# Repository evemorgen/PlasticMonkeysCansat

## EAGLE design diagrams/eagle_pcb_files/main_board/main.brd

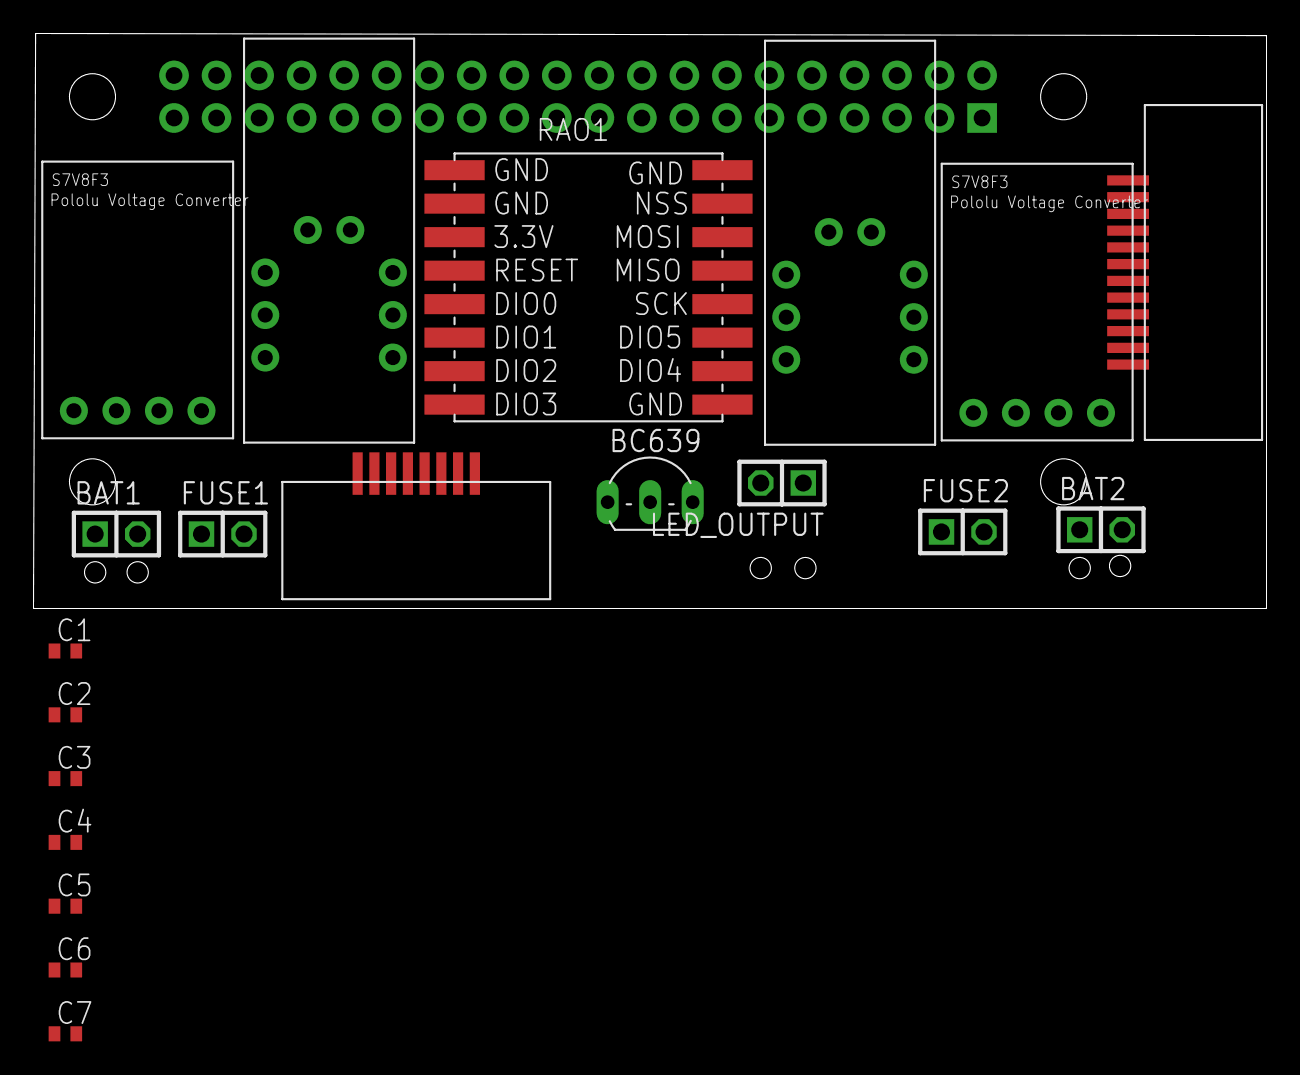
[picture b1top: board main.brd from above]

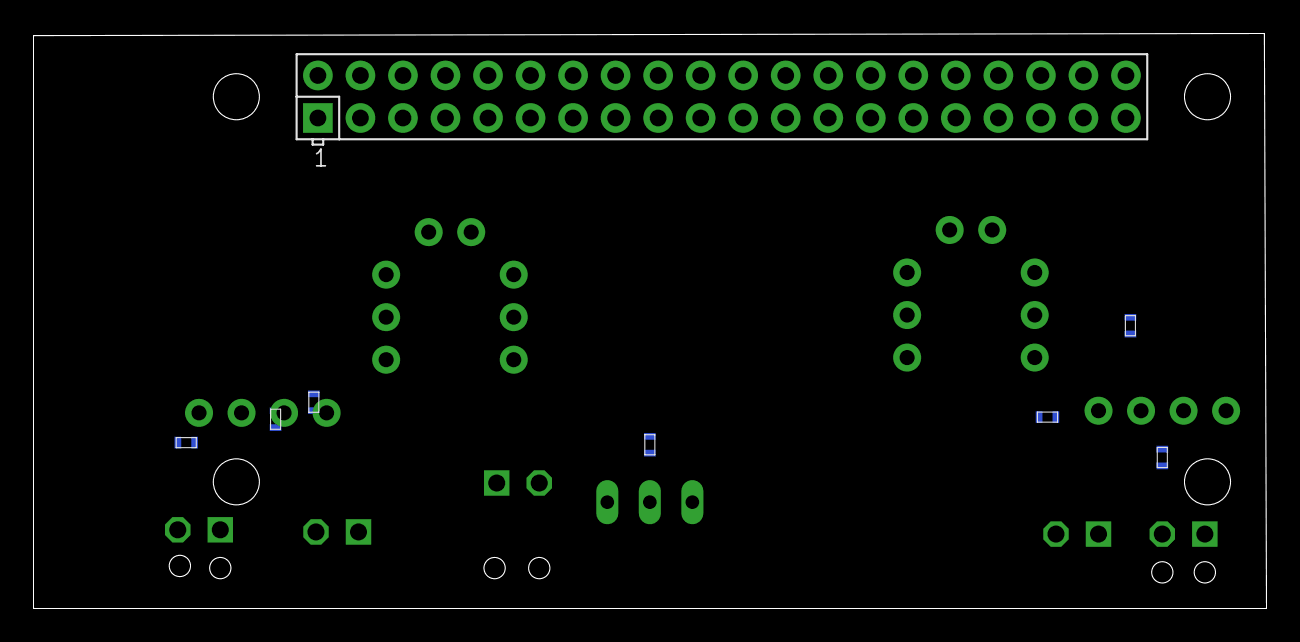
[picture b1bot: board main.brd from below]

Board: 2 copper layers, 73.6 x 34.3 mm, 28 parts (8 on the bottom side), 31 nets, no tracks yet.

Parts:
BAT1, BAT2: 1X02
BC639: BCX59SMD; TO92-EBC
C1, C2, C3, C4, C5, C6, C7: C0402
D1: DIODE1206; 1206
FUSE1, FUSE2: 1X02
LED_OUTPUT: 1X02
R1: RESISTOR1206; 1206
RAO1: LORA-RA-02-433MHZ; LORA-RA2-SMD
RAO2: RPI-ZERO; RASPBERRYPI_BASTELSTUBE_V13_RASPI_BOARD_B+_FULL
RAO3, RAO4: S7V8F3
U$1: TYCO_8PIN_1MM_SMD; TYCO_1MM_8PIN
U$2: TYCO_12PIN_1MM_SMD; TYCO_1MM_12PIN
U$3, U$9: POLOLU_FUEL_GAUGEBREAKBOARD; BREAKBOARD
U$4, U$7, U$8: DIODE1206; 1206
U$5, U$6: SMD_COMPONENT1206; 1206

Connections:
3.3V: C1.2, C2.1, C3.1, C4.1, C5.2, C6.1, C7.1, LED_OUTPUT.2, RAO1.3, RAO2.17, U$1.P$1, U$2.P$1, U$3.VCC, U$4.P$2, U$7.P$2, U$9.VCC
B1: RAO2.29, U$1.P$7
B2: RAO2.31, U$1.P$6
B3: RAO2.33, U$1.P$5
BIN1: BAT1.2, D1.P$1
BIN2: BAT2.2, U$8.P$1
DIO0: RAO1.5, RAO2.7
DIO1: RAO1.6, RAO2.11
DIO2: RAO1.7, RAO2.12
DIO3: RAO1.8, RAO2.13
G1: RAO2.35, U$2.P$10
G2: RAO2.32, U$2.P$11
G3: RAO2.18, U$2.P$12
GND: BAT1.1, BAT2.1, BC639.E, C1.1, C2.2, C3.2, C4.2, C5.1, C6.2, C7.2, RAO1.1, RAO1.2, RAO1.9, RAO1.16, RAO2.25, RAO3.GND, RAO4.GND, U$1.P$2, U$2.P$2, U$3.-, U$3.GND, U$5.P$1, U$6.P$1, U$9.-, U$9.GND
LED: R1.P$1, RAO2.16
MISO: RAO1.13, RAO2.21, U$2.P$6
MOSI: RAO1.14, RAO2.19, U$2.P$5
unnamed: BC639.B, R1.P$2
unnamed: FUSE2.2, U$6.P$2, U$7.P$1
unnamed: FUSE1.2, U$4.P$1, U$5.P$2
unnamed: BC639.C, LED_OUTPUT.1
NSS: RAO1.15, RAO2.24, U$2.P$8
RESET: RAO1.4, RAO2.15
SCK: RAO1.12, RAO2.23, U$2.P$7
SCL: RAO2.5, U$1.P$3, U$2.P$3, U$3.SCL, U$9.SCL
SDA: RAO2.3, U$1.P$4, U$2.P$4, U$3.SDA, U$9.SDA
SS2: RAO2.26, U$2.P$9
VIN1: D1.P$2, RAO3.VIN, U$3.+
VIN2: RAO4.VIN, U$8.P$2, U$9.+
VOUT1: FUSE1.1, RAO3.VOUT
VOUT2: FUSE2.1, RAO4.VOUT

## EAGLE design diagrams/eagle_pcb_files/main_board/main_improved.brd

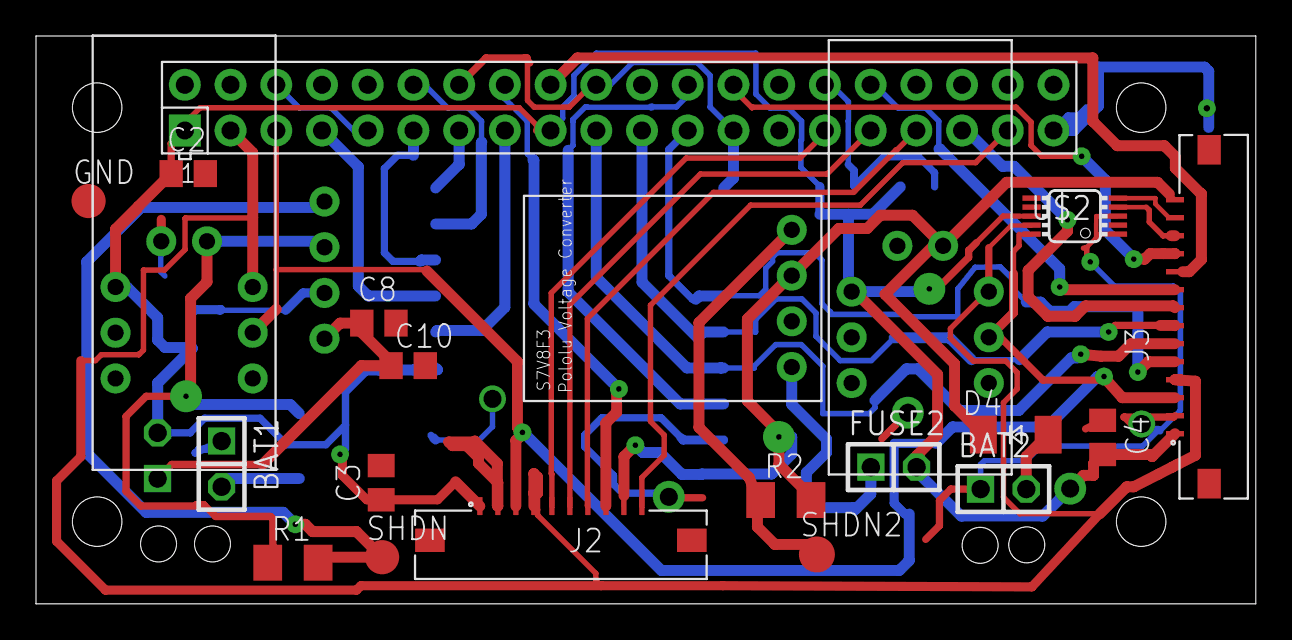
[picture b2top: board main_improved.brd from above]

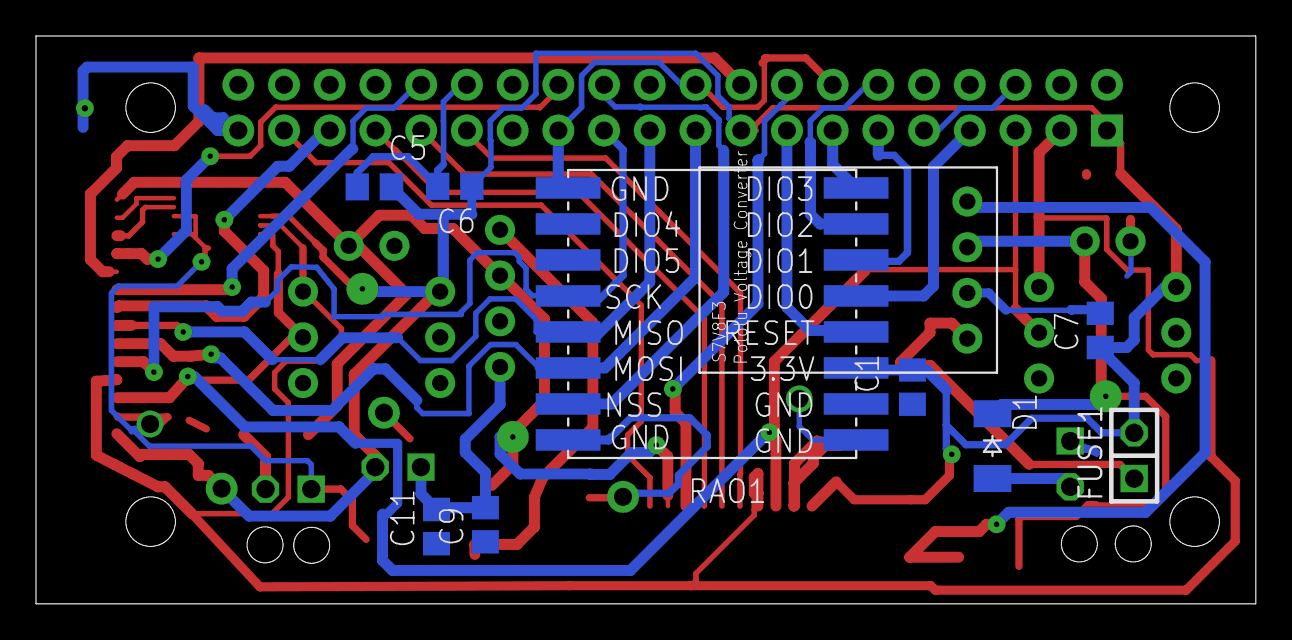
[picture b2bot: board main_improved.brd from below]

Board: 2 copper layers, 67.8 x 31.5 mm, 31 parts (10 on the bottom side), 32 nets.

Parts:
BAT1, BAT2: 1X02
C1, C2, C3, C4, C5, C6, C7: 100nF; C0805
C8, C9: 100 nF; C0805
C10, C11: 10 uF; C0805
D1, D4: CGRM4001-G; SOD-123_MINI-SMA
FUSE1, FUSE2: 1X02
GND: TPTP19R; TP19R
J2: 686110183522
J3: 686114183522
R1, R2: 4.7k; M1206
RAO1: LORA-RA-02-433MHZ; LORA-RA2-SMD
RAO2: RPI-ZERO; RASPBERRYPI_BASTELSTUBE_V13_RASPI_BOARD_B+_FULL
RAO3, RAO4: S7V8F3
SHDN: TPTP19R; TP19R
SHDN2: TPTP20R; TP20R
U$2: ADS1015IDGT; MSOP10_0.5
U$3, U$9: POLOLU_FUEL_GAUGEBREAKBOARD; BREAKBOARD

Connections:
3.3V: C1.2, C2.1, C3.1, C4.2, C5.2, C6.1, C7.1, FUSE1.2, FUSE2.2, J2.1, J3.1, RAO1.3, RAO2.1, RAO2.17, U$2.8, U$3.VCC, U$9.VCC
A0: J3.12, U$2.4
A1: J3.13, U$2.5
B1: J2.7, RAO2.33
B2: J2.6, RAO2.31
B3: J2.5, RAO2.29
BIN1: BAT1.2, D1.A
BIN2: BAT2.2, D4.A
BUZ: J2.10, RAO2.37
DIO0: RAO1.5, RAO2.7
DIO1: RAO1.6, RAO2.11
DIO2: RAO1.7, RAO2.12
DIO3: RAO1.8, RAO2.13
G1: J3.8, RAO2.35
G2: J3.9, RAO2.32
G3: J3.10, RAO2.18
GND: BAT1.1, BAT2.1, C1.1, C2.2, C3.2, C4.1, C5.1, C6.2, C7.2, C8.2, C9.1, C10.2, C11.1, GND.TP, J2.2, J3.2, RAO1.1, RAO1.2, RAO1.9, RAO1.16, RAO2.6, RAO2.9, RAO2.14, RAO2.20, RAO2.25, RAO2.30, RAO2.34, RAO2.39, RAO3.GND, RAO4.GND, U$2.1, U$2.3, U$3.-, U$3.GND, U$9.-, U$9.GND
LED: J2.8, RAO2.16
MISO: J3.7, RAO1.13, RAO2.21
MOSI: J3.6, RAO1.14, RAO2.19
NSS: RAO1.15, RAO2.24
RESET: RAO1.4, RAO2.15
SCK: J3.5, RAO1.12, RAO2.23
SCL: J2.3, J3.3, RAO2.5, U$2.10, U$3.SCL, U$9.SCL
SDA: J2.4, J3.4, RAO2.3, U$2.9, U$3.SDA, U$9.SDA
SHDN: RAO3.SHDN, SHDN.TP
SHDN2: RAO4.SHDN, SHDN2.TP
SS1: J3.11, RAO2.26
VIN1: D1.C, RAO3.VIN, U$3.+
VIN2: D4.C, J2.9, J3.14, RAO4.VIN, U$9.+
VOUT1: C8.1, C10.1, FUSE1.1, RAO3.VOUT
VOUT2: C9.2, C11.2, FUSE2.1, RAO4.VOUT

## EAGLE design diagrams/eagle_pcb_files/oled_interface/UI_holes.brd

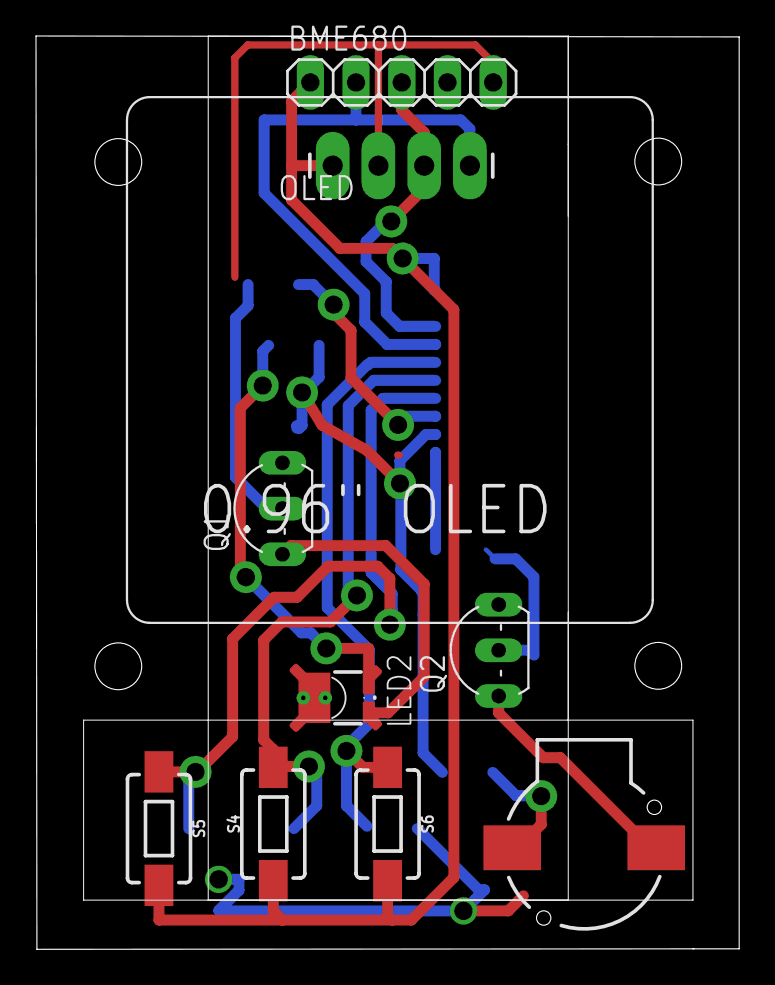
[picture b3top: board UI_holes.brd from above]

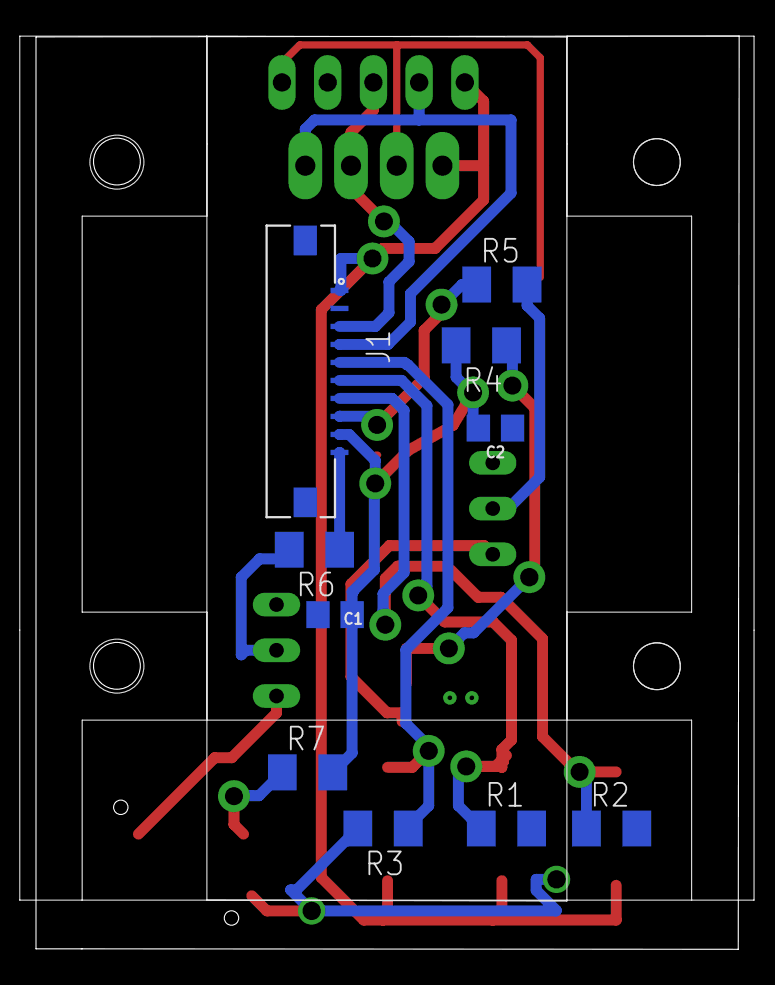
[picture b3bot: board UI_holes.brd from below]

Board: 2 copper layers, 39.1 x 50.7 mm, 19 parts (10 on the bottom side), 15 nets.

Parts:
B1: Buzzer; BUZZER-CCV
BME680: 1X05
C1, C2: C0805
J1: 686110183422
LED2: LUXEON_REBEL
OLED: I2C_OLED; I2C_OLED_PACKAGE
Q1, Q2: BCX59SMD; TO92-EBC
R1, R2, R3, R5, R6: 10k; M1206
R4: 10R; M1206
R7: 200R; M1206
S4, S5, S6: MOMENTARY-SWITCH-SPST-SMD-6.0X3.5MM; TACTILE_SWITCH_SMD_6.0X3.5MM

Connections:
B1: J1.7, R2.1, S5.1
B2: J1.6, R1.1, S4.2
B3: J1.5, R3.1, S6.1
BUZ: J1.10, R6.1
GND: BME680.5, C1.1, C2.1, J1.2, OLED.2, Q1.E, Q2.E, R1.2, R2.2, R3.2
LED: J1.8, R5.1
unnamed: LED2.A, LED2.A@1, R4.1
unnamed: LED2.C, LED2.C@1, Q1.C
unnamed: Q1.B, R5.2
unnamed: Q2.B, R6.2
SCL: BME680.3, J1.3, OLED.3
SDA: BME680.2, J1.4, OLED.4
TH: LED2.TH, LED2.TH@1, LED2.TH@2, LED2.TH@3, LED2.TH@4
VCC: BME680.1, J1.1, OLED.1, S4.1, S5.2, S6.2
VIN1: C1.2, C2.2, J1.9, R4.2, R7.2

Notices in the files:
parts and their libraries:
Wurth_Elektronik_Electromechanic_FPC_Con: Copyright: Würth Elektronik
SparkFun-Switches: Licensing: Creative Commons ShareAlike 4.0 International - https://creativecommons.org/licenses/by-sa/4.0
